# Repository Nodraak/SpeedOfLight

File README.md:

# Speed of light

*Reenactment of experiment(s) to measure the speed of light.*

Following a [video by AlphaPhenix in 2018](https://www.youtube.com/watch?v=YMO9uUsjXaI), where he redo Fizeau's experiement, I set out to reenact the experiement myself.
After some research, it seems to me that Foucault's experiement is easier to perform and will give a more precise value, while using a somehow similar technique.

(Incomplete) history of speed of light measurements from [Wikipedia](https://en.wikipedia.org/wiki/Speed_of_light#Measurement):

| Scientist | Experiment                                | Year | Value measured (accuracy)                  |
|-----------|-------------------------------------------|------|--------------------------------------------|
| Rømer     | Jupiter vs Io timing                      | 1676 | Earth's orbit's diameter / 22 min          |
| Bradley   | Aberration of light from a distant star   | 1729 | Sun to the Earth distance / 8 min 12 sec   |
| Fizeau    | Time of flight with a toothed wheel       | 1848 | 313 274 304 m/s (4.5%)                     |
| Foucault  | Time of flight with a mirror              | 1862 | 298 000 000 m/s (0.6%)                     |
| Cornu     | Refinement of Fizeau's                    | 1872 | 300 400 000 m/s (0.2%)                     |
| Michelson | Refinement of Foucault's                  | 1879 | 299 944 000 m/s (0.05%)                    |

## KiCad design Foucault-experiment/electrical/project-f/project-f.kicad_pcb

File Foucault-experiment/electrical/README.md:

# Electrical

## Introduction

*A small PCB to connect all the components cleanly, 80x100 mm.*

The following components will be used:

* Electric motor + ESC: Power (12V), PWM
* Light sensor: Power, signal
* ESP32 (5V)
* Step down 12V to 5V

## Notes

### MCU

* ESP32 WROOM 32
* AZ Delivery ESP32 DevKitC v4

### KY-018

LDR-resistor (Light dependent resistor), which decreases its resistance at brighter surrounding

Pinout:
* GND
* V+ (5V)
* Signal

```c
int rawValue = analogRead(sensorPin);
float voltage_v = rawValue * (5.0 / 1023);
float resistance = 10 * voltage_v / ( 5.0 - voltage_v);
```

### ESC

Power rating:

* Max 150 W -> @12 V = 12 A
* Max 13 A for 60 sec

PWM control:

50 Hz PWM (20 ms): 20 ms low + 1-2 ms active

### PSU

* Wall mounted: 12 V * 2 A = 24 W
* Lab: 30 V * 10 A = 300 W

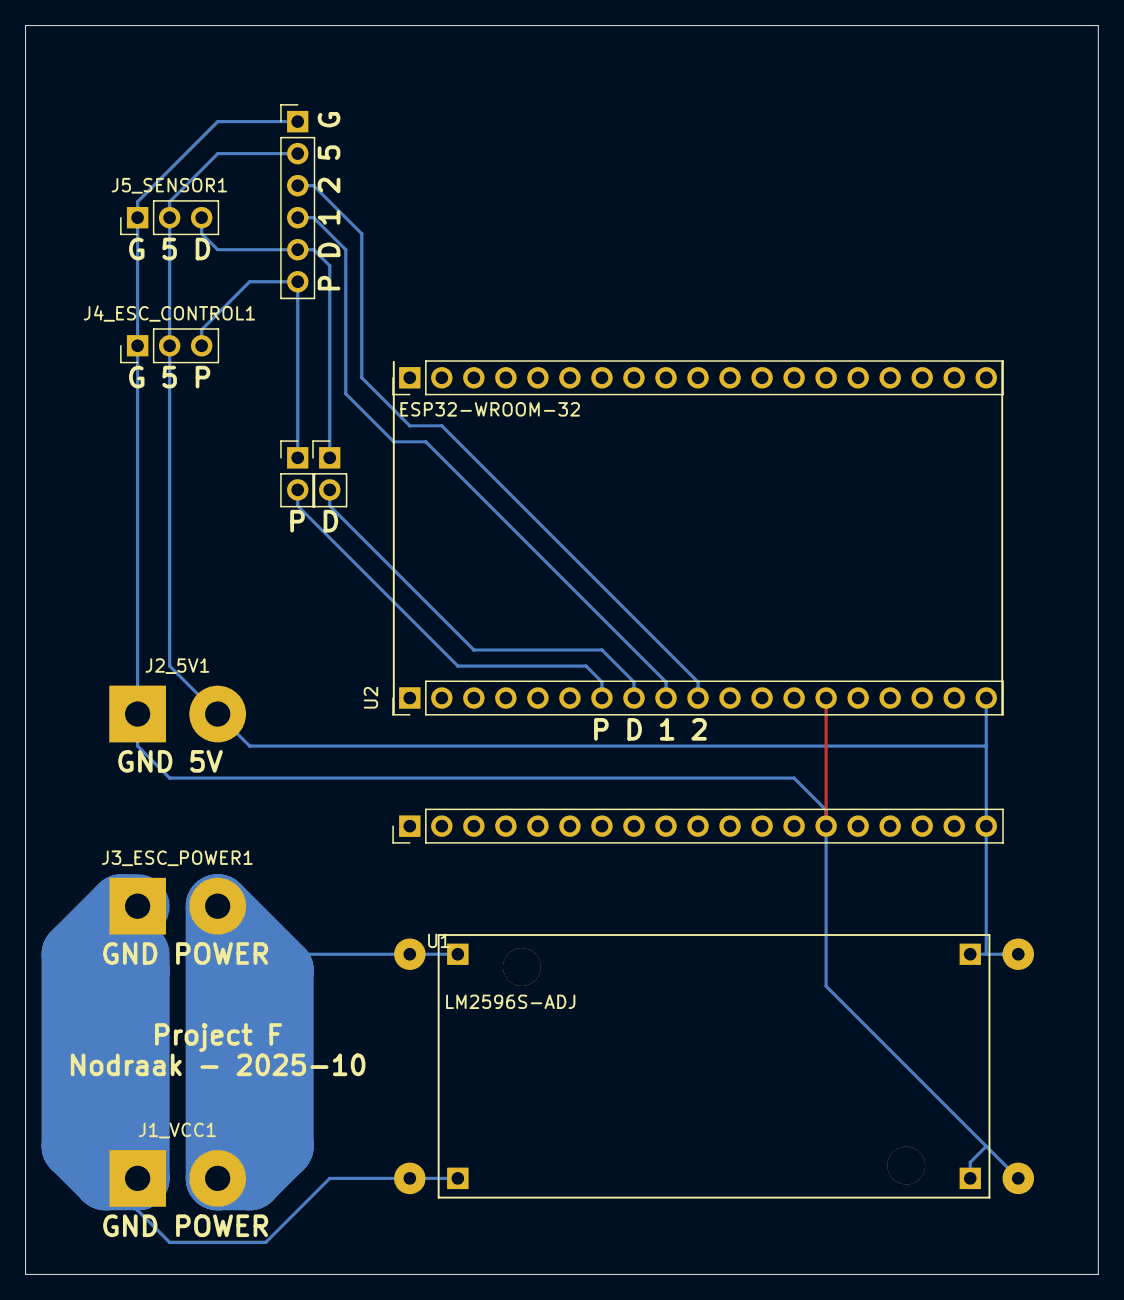
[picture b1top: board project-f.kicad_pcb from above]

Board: 2 copper layers, 85.1 x 99.1 mm, 7 parts (0 on the bottom side), 6 nets.

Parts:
J1_VCC1, J2_5V1, J3_ESC_POWER1: Conn_01x02; SolderWirePad_1x02_P7.62mm_Drill2mm
J4_ESC_CONTROL1, J5_SENSOR1: Conn_01x03; PinHeader_1x03_P2.54mm_Vertical
U1: LM2596S-ADJ; AZ-LM2596S
U2: ESP32-WROOM-32; ESP32_DevkitC

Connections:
+5V: J2_5V1.2, J4_ESC_CONTROL1.2, J5_SENSOR1.2, U1.4, U2.2
+VDC: J1_VCC1.2, J3_ESC_POWER1.2, U1.1
/ESC_PWM: J4_ESC_CONTROL1.3, U2.8
/Sensor_signal: J5_SENSOR1.3, U2.9
GND: J2_5V1.1, J4_ESC_CONTROL1.1, J5_SENSOR1.1, U1.2, U2.1, U2.15, U2.38
GNDPWR: J1_VCC1.1, J3_ESC_POWER1.1, U1.3

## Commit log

2025-11-09 Initial commit
    * README.md, .gitignore
    * Fizeau notes
    * Foucault
    * Mechanical: mirror holder (OpenScad)
    * Electrical: PCB, datasheets/pinouts
    * Software: notes
2025-11-09 WIP - SW
2025-11-11 Introduce HAL (WIP)
    Next steps:
    * Introduce platform (Arduino/Linux) headers
    * Implement non blocking read on Linux
    * Implement timer on Linux
    * Implement abstraction for statistics (store samples, compute and print deciles)
    * Integrated test on Linux
2025-11-12 Introduce platform (Arduino/Linux) headers and finish fixing warnings/errors
2025-11-13 Implement abstraction for statistics
    Next steps:
    * Implement non blocking read on Linux
    * Implement timer on Linux
    * Adjust code with nod_stats_t
    * Integrated test on Linux
    * Unit test each function on HW
2025-11-14 Cleanup and fix the code
    * Properly implement arrays of samples, rev duration and IRQ duration with mutex handling
    * Add a few new APIs
    * Fix a few bugs
    * Timing analysis of current solution (continuous ADC sampling) shows a max of 4 k RPM
    * The requirement is absolute minimum 10 k RPM and stretch goal 100 k RPM
    * Can use GPIO IRQ, but this requires signal conditioning to digitalize the analog signal
2025-11-17 Cleanup and fix the code 2/2
    * Properly implement dynamic threshold
    * median value => Garbage, can not work when distribution is 99/1
    * Basic average => Does not work. Can not work when distribution is 99/1?
    * Fancy weighted average => a bit more complex, but seems ok
    * Fix a few bugs
2025-11-18 Cleanup and improve HAL, fix nod_stats, add simulated ADC data, update README.md
2025-11-22 Implement Timer HAL for Linux (background thread)
    Next steps:
    * Do more testing on Linux and fix some bugs
    * Test on HW
2025-11-29 Rework simulated ADC data for Linux and fix a few issues
    Fix:
    * Fix infinite loop when computing deciles on empty data
    * Fix rev duration calculation
    * Fix rev duration us vs ms
    Next steps:
    * Fix bug when simulated data is high and threashold does not readjust
2025-11-29 REWORD - mech
2025-11-29 REWORD sw
    * c -> ino (wtf arduino!)
    * create links to have all files in same folder (wtf arduino!)
    * typedef do not work? (wtf arduino!)
    * delete unnecessary includes (wtf arduino!)
    * fix pwm duty calculation - rounded to 0
    * improve timer API (more human friendly, less leaky)
2025-11-29 DEBUG SW PWM
2025-12-02 Mechanical: fix miror width, and add 3D printing details
2025-12-02 Software: testing on HW, various fixes
    * Arduino: Rename .c to .ino (wtf arduino!)
    * Arduino: Create symlinks to have all the files in same folder (wtf arduino!)
    * Arduino: Typedef (`nod_stats_t`) do not work? (wtf arduino!)
    * Arduino: Delete unnecessary includes (Arduino and esp) (wtf arduino!)
    * Fix: PWM duty calculation - was rounded to 0 due to integer division
    * Improve: timer API (more human friendly, less leaky abstraction)
2026-02-15 Mechanical: create Main Assembly (top + bottom)
2026-02-23 Mechanical: main assembly: fix 5 bugs
    * Laser holder diameter 12 -> 13
    * Corner holes between top and bottom assemblies -> screw holes
    * Motor holder holes -> fix
    * Mirror holder cylinder size: 50 -> 44
    * Light shafts diameter: 5 -> 3
2026-02-23 Mechanical: main assembly: add camera holder
2026-02-23 Mechanical: main assembly: update stl and png files
